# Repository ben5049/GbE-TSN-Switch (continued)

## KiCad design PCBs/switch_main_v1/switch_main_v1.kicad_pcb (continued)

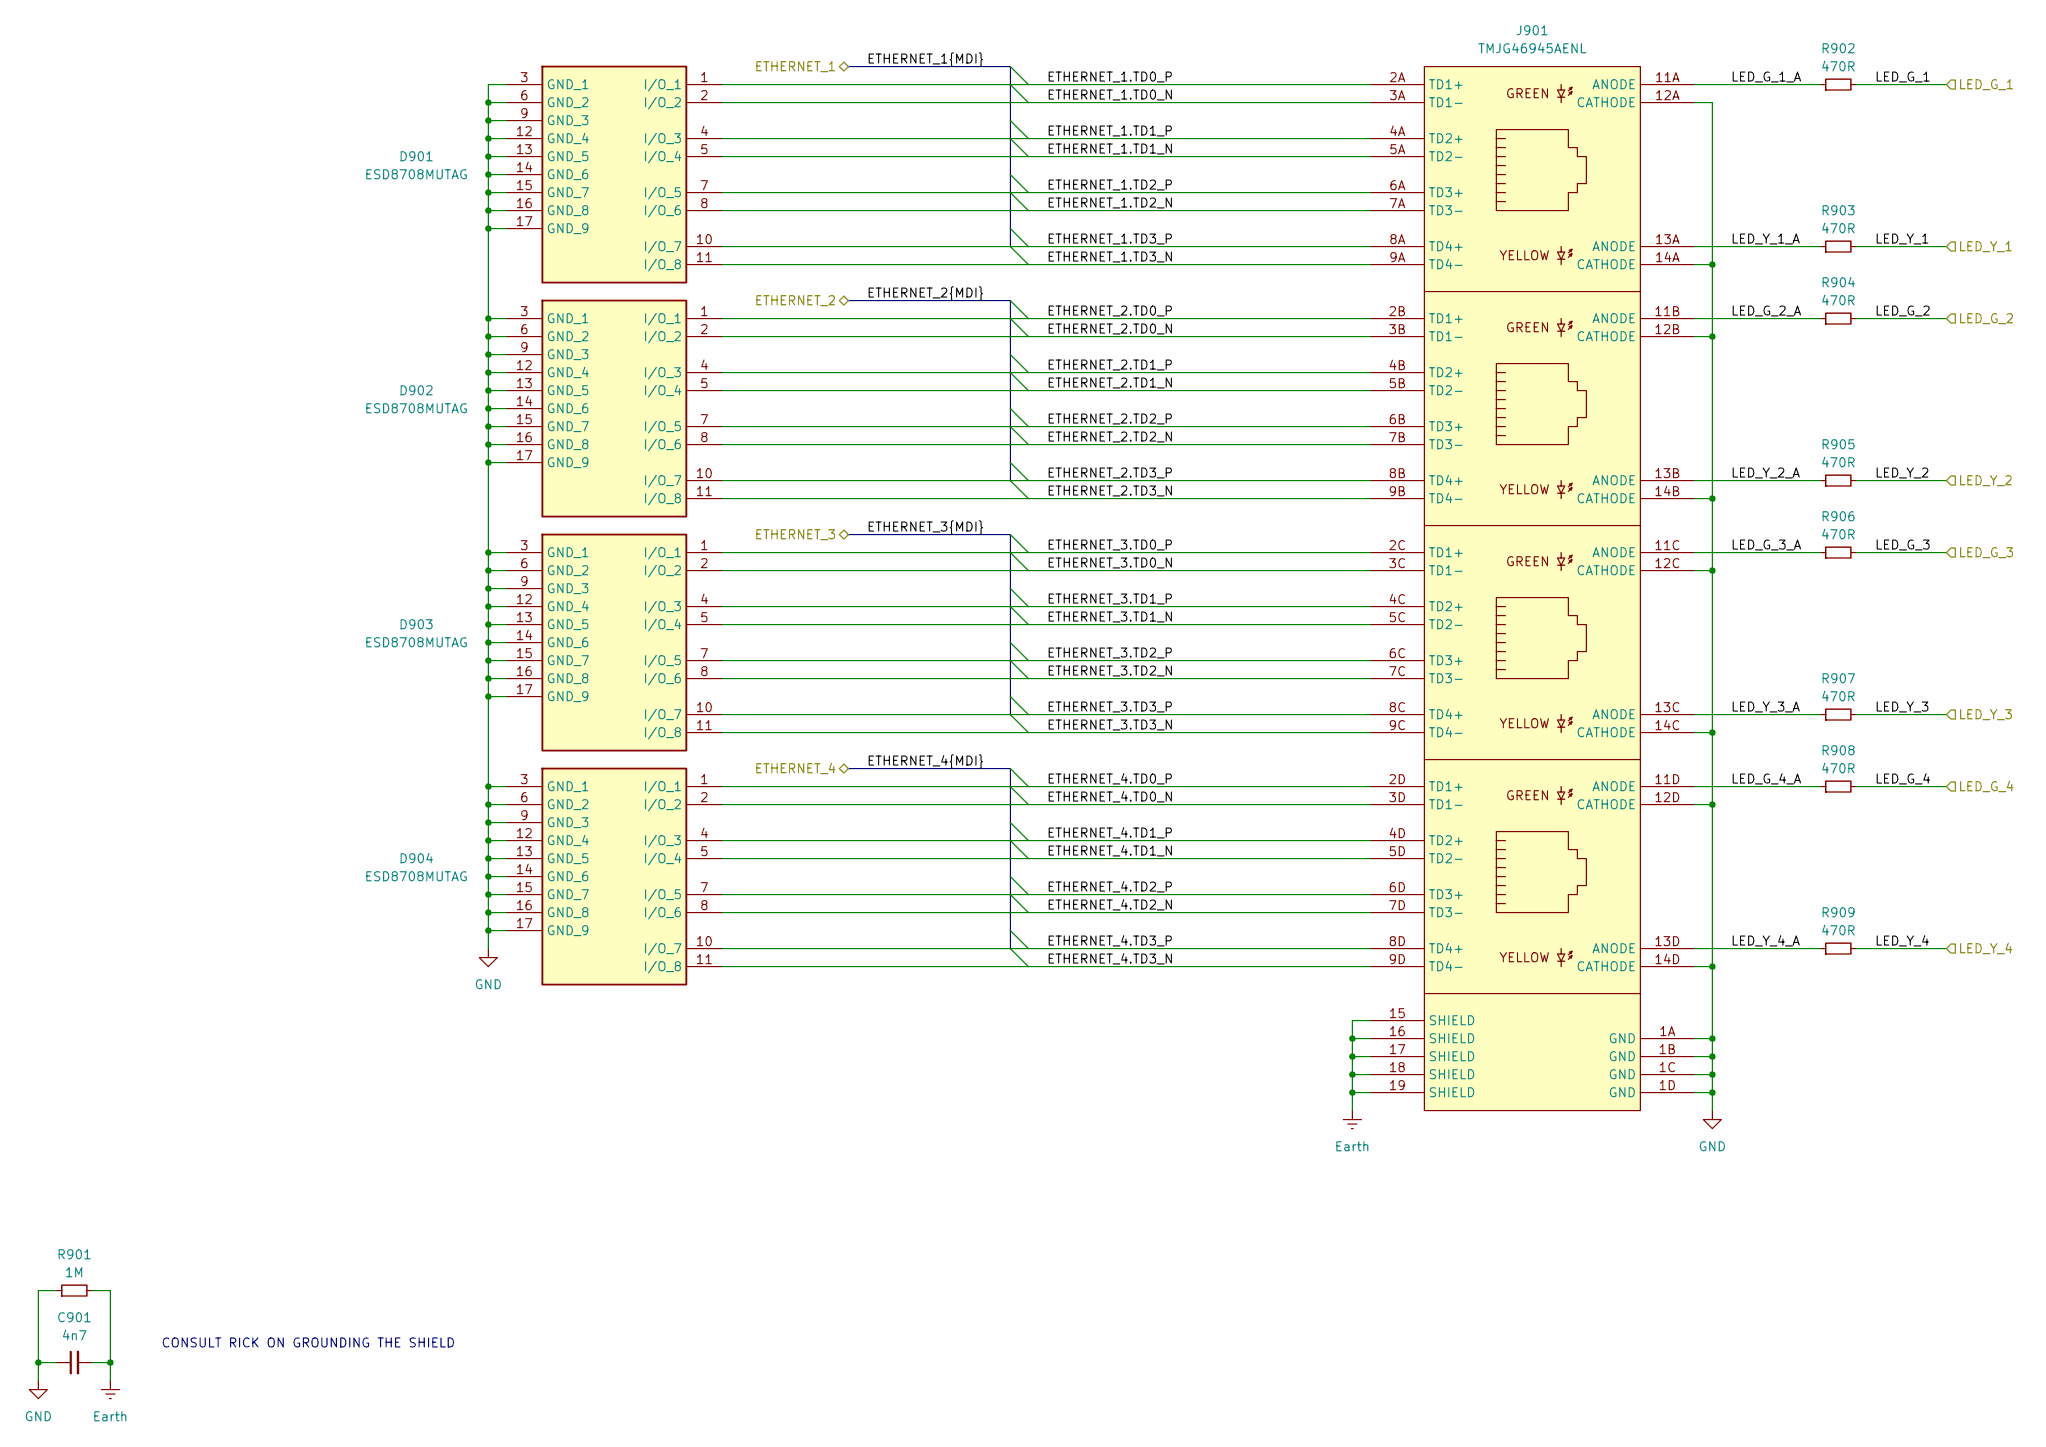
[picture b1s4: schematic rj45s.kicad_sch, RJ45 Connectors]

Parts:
C901: 4n7; C_0402_1005Metric
D901, D902, D903, D904: ESD8708MUTAG; Mouser Part Number 863-ESD8708MUTAG
J901: TMJG46945AENL
R901: 1M; R_0402_1005Metric
R902, R903, R904, R905, R906, R907, R908, R909: 470R; R_0402_1005Metric

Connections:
/ETHERNET_1.TD0_N: D901.2 (I/O_2), J901.3A (TD1-); also elsewhere on the board
/ETHERNET_1.TD0_P: D901.1 (I/O_1), J901.2A (TD1+); also elsewhere on the board
/ETHERNET_1.TD1_N: D901.5 (I/O_4), J901.5A (TD2-); also elsewhere on the board
/ETHERNET_1.TD1_P: D901.4 (I/O_3), J901.4A (TD2+); also elsewhere on the board
/ETHERNET_1.TD2_N: D901.8 (I/O_6), J901.7A (TD3-); also elsewhere on the board
/ETHERNET_1.TD2_P: D901.7 (I/O_5), J901.6A (TD3+); also elsewhere on the board
/ETHERNET_1.TD3_N: D901.11 (I/O_8), J901.9A (TD4-); also elsewhere on the board
/ETHERNET_1.TD3_P: D901.10 (I/O_7), J901.8A (TD4+); also elsewhere on the board
/ETHERNET_2.TD0_N: D902.2 (I/O_2), J901.3B (TD1-); also elsewhere on the board
/ETHERNET_2.TD0_P: D902.1 (I/O_1), J901.2B (TD1+); also elsewhere on the board
/ETHERNET_2.TD1_N: D902.5 (I/O_4), J901.5B (TD2-); also elsewhere on the board
/ETHERNET_2.TD1_P: D902.4 (I/O_3), J901.4B (TD2+); also elsewhere on the board
/ETHERNET_2.TD2_N: D902.8 (I/O_6), J901.7B (TD3-); also elsewhere on the board
/ETHERNET_2.TD2_P: D902.7 (I/O_5), J901.6B (TD3+); also elsewhere on the board
/ETHERNET_2.TD3_N: D902.11 (I/O_8), J901.9B (TD4-); also elsewhere on the board
/ETHERNET_2.TD3_P: D902.10 (I/O_7), J901.8B (TD4+); also elsewhere on the board
/ETHERNET_3.TD0_N: D903.2 (I/O_2), J901.3C (TD1-); also elsewhere on the board
/ETHERNET_3.TD0_P: D903.1 (I/O_1), J901.2C (TD1+); also elsewhere on the board
/ETHERNET_3.TD1_N: D903.5 (I/O_4), J901.5C (TD2-); also elsewhere on the board
/ETHERNET_3.TD1_P: D903.4 (I/O_3), J901.4C (TD2+); also elsewhere on the board
/ETHERNET_3.TD2_N: D903.8 (I/O_6), J901.7C (TD3-); also elsewhere on the board
/ETHERNET_3.TD2_P: D903.7 (I/O_5), J901.6C (TD3+); also elsewhere on the board
/ETHERNET_3.TD3_N: D903.11 (I/O_8), J901.9C (TD4-); also elsewhere on the board
/ETHERNET_3.TD3_P: D903.10 (I/O_7), J901.8C (TD4+); also elsewhere on the board
/ETHERNET_4.TD0_N: D904.2 (I/O_2), J901.3D (TD1-); also elsewhere on the board
/ETHERNET_4.TD0_P: D904.1 (I/O_1), J901.2D (TD1+); also elsewhere on the board
/ETHERNET_4.TD1_N: D904.5 (I/O_4), J901.5D (TD2-); also elsewhere on the board
/ETHERNET_4.TD1_P: D904.4 (I/O_3), J901.4D (TD2+); also elsewhere on the board
/ETHERNET_4.TD2_N: D904.8 (I/O_6), J901.7D (TD3-); also elsewhere on the board
/ETHERNET_4.TD2_P: D904.7 (I/O_5), J901.6D (TD3+); also elsewhere on the board
/ETHERNET_4.TD3_N: D904.11 (I/O_8), J901.9D (TD4-); also elsewhere on the board
/ETHERNET_4.TD3_P: D904.10 (I/O_7), J901.8D (TD4+); also elsewhere on the board
/LED_G_1: R902.2; also elsewhere on the board
/LED_G_2: R904.2; also elsewhere on the board
/LED_G_3: R906.2; also elsewhere on the board
/LED_G_4: R908.2; also elsewhere on the board
/LED_Y_1: R903.2; also elsewhere on the board
/LED_Y_2: R905.2; also elsewhere on the board
/LED_Y_3: R907.2; also elsewhere on the board
/LED_Y_4: R909.2; also elsewhere on the board
/RJ45s/LED_G_1_A: J901.11A (ANODE), R902.1
/RJ45s/LED_G_2_A: J901.11B (ANODE), R904.1
/RJ45s/LED_G_3_A: J901.11C (ANODE), R906.1
/RJ45s/LED_G_4_A: J901.11D (ANODE), R908.1
/RJ45s/LED_Y_1_A: J901.13A (ANODE), R903.1
/RJ45s/LED_Y_2_A: J901.13B (ANODE), R905.1
/RJ45s/LED_Y_3_A: J901.13C (ANODE), R907.1
/RJ45s/LED_Y_4_A: J901.13D (ANODE), R909.1
Earth: C901.2, J901.15 (SHIELD), J901.16 (SHIELD), J901.17 (SHIELD), J901.18 (SHIELD), J901.19 (SHIELD), R901.2; also elsewhere on the board
GND: C901.1, D901.3 (GND_1), D901.6 (GND_2), D901.9 (GND_3), D901.12 (GND_4), D901.13 (GND_5), D901.14 (GND_6), D901.15 (GND_7), D901.16 (GND_8), D901.17 (GND_9), D902.3 (GND_1), D902.6 (GND_2), D902.9 (GND_3), D902.12 (GND_4), D902.13 (GND_5), D902.14 (GND_6), D902.15 (GND_7), D902.16 (GND_8), D902.17 (GND_9), D903.3 (GND_1), D903.6 (GND_2), D903.9 (GND_3), D903.12 (GND_4), D903.13 (GND_5), D903.14 (GND_6), D903.15 (GND_7), D903.16 (GND_8), D903.17 (GND_9), D904.3 (GND_1), D904.6 (GND_2), D904.9 (GND_3), D904.12 (GND_4), D904.13 (GND_5), D904.14 (GND_6), D904.15 (GND_7), D904.16 (GND_8), D904.17 (GND_9), J901.1A (GND), J901.1B (GND), J901.1C (GND), J901.1D (GND), J901.12A (CATHODE), J901.12B (CATHODE), J901.12C (CATHODE), J901.12D (CATHODE), J901.14A (CATHODE), J901.14B (CATHODE), J901.14C (CATHODE), J901.14D (CATHODE), R901.1; also elsewhere on the board

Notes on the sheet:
CONSULT RICK ON GROUNDING THE SHIELD

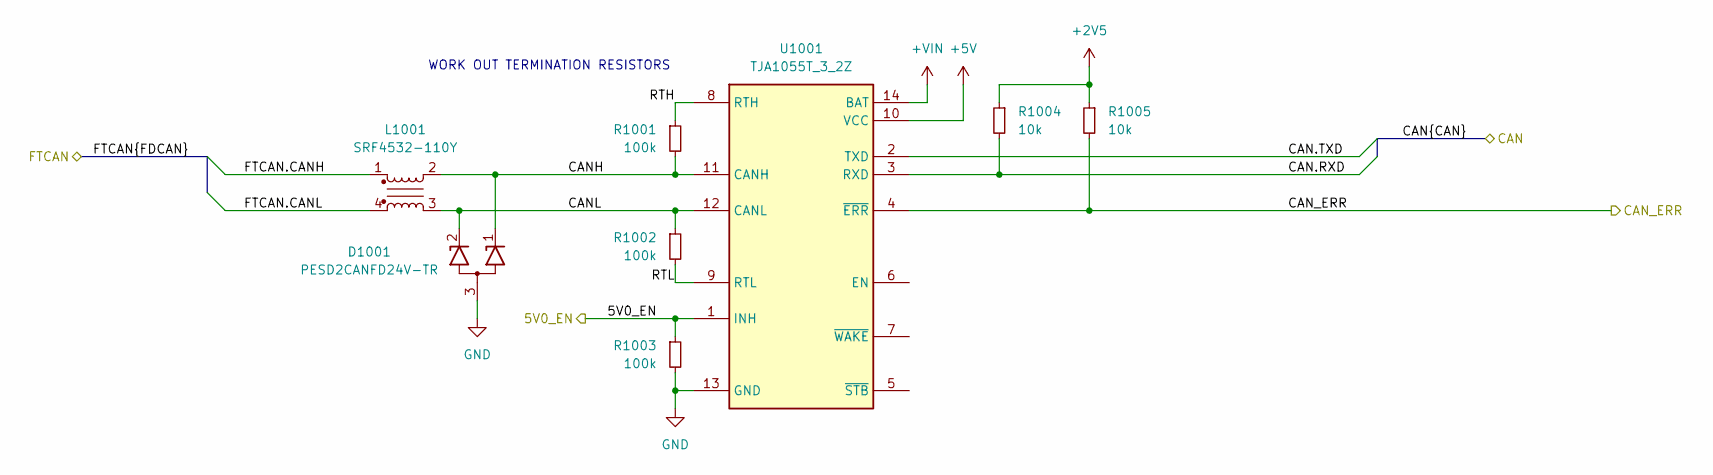
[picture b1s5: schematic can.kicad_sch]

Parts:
D1001: PESD2CANFD24V-TR; SOT95P230X110-3N; Mouser Part Number 771-PESD2CANFD24V-TR
L1001: SRF4532-110Y; SRF4532101Y; Mouser Part Number 652-SRF4532-110Y
R1001, R1002, R1003: 100k; R_0402_1005Metric
R1004, R1005: 10k; R_0402_1005Metric
U1001: TJA1055T_3_2Z; SOIC127P600X175-14N; Mouser Part Number 771-TJA1055T/3/2Z

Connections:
+2V5: R1004.1, R1005.1; also elsewhere on the board
+5V: U1001.10 (VCC)
+VIN: U1001.14 (BAT); also elsewhere on the board
/5V0_EN: R1003.1, U1001.1 (INH); also elsewhere on the board
/CAN.RXD: R1004.2, U1001.3 (RXD); also elsewhere on the board
/CAN.TXD: U1001.2 (TXD); also elsewhere on the board
/CAN/CANH: D1001.1 (K1), L1001.2, R1001.2, U1001.11 (CANH)
/CAN/CANL: D1001.2 (K2), L1001.3, R1002.1, U1001.12 (CANL)
/CAN/CAN_ERR: R1005.2, U1001.4 (~ERR)
/CAN/FTCAN.CANH: L1001.1
/CAN/FTCAN.CANL: L1001.4
/CAN/RTH: R1001.1, U1001.8 (RTH)
/CAN/RTL: R1002.2, U1001.9 (RTL)
GND: D1001.3 (CC), R1003.2, U1001.13 (GND); also elsewhere on the board

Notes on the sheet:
WORK OUT TERMINATION RESISTORS

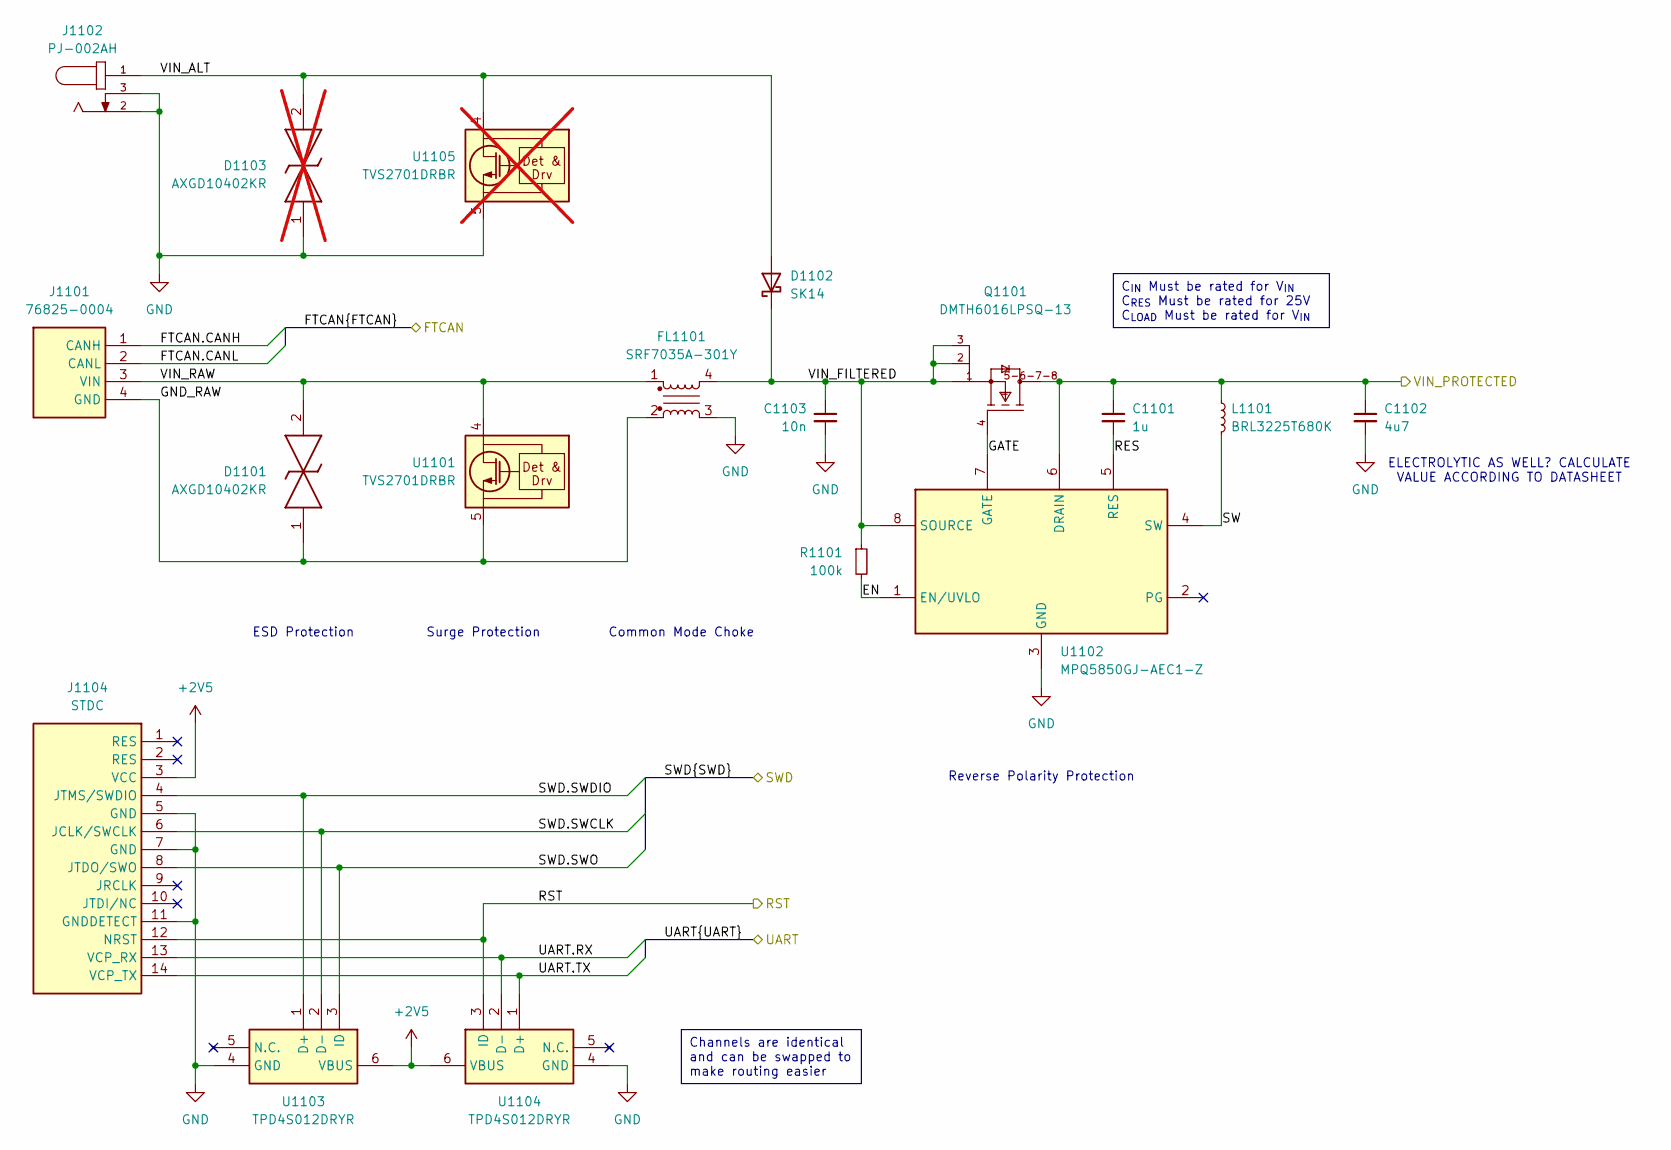
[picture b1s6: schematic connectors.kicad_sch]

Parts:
C1101: 1u; C_0402_1005Metric
C1102: 4u7; C_0402_1005Metric
C1103: 10n; C_0402_1005Metric
D1101: AXGD10402KR; DIONM105X51N; Mouser Part Number 576-AXGD10402KR
D1102: SK14; D_SMA
D1103: AXGD10402KR; DIONM105X51N; Mouser Part Number 576-AXGD10402KR; not fitted
FL1101: SRF7035A-301Y; SRF7035A301Y; Mouser Part Number 652-SRF7035A-301Y
J1101: 76825-0004; 768250004; Mouser Part Number 538-76825-0004
J1102: PJ-002AH; CUI_PJ-002AH
J1104: STDC; STDC14
L1101: BRL3225T680K; L_1210_3225Metric
Q1101: DMTH6016LPSQ-13; Diodes_Incorporated-PowerDI5060-8-03_2017-0-MFG; mouser part number 621-DMTH6016LPSQ-13; digikey description MOSFET N-CHA 60V 10.6A POWERDI
R1101: 100k; R_0402_1005Metric
U1101: TVS2701DRBR; SON65P300X300X100-9N-D; Mouser Part Number 595-TVS2701DRBR
U1102: MPQ5850GJ-AEC1-Z; SOT65P280X100-8N; Manufacturer_Part_Number MPQ5850GJ-AEC1-Z
U1103, U1104: TPD4S012DRYR; Mouser Part Number 595-TPD4S012DRYR
U1105: TVS2701DRBR; SON65P300X300X100-9N-D; Mouser Part Number 595-TVS2701DRBR; not fitted

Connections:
+2V5: J1104.3 (VCC), U1103.6 (VBUS), U1104.6 (VBUS); also elsewhere on the board
/Connectors/EN: R1101.2, U1102.1 (EN/UVLO)
/Connectors/GATE: Q1101.4 (G), U1102.7 (GATE)
/Connectors/GND_RAW: D1101.1, FL1101.2, J1101.4 (GND), U1101.5 (GND), U1101.6 (GND), U1101.7 (GND), U1101.8 (GND)
/Connectors/RES: C1101.2, U1102.5 (RES)
/Connectors/SW: L1101.2, U1102.4 (SW)
/Connectors/VIN_ALT: D1102.2 (A), D1103.2, J1102.1, U1105.1 (IN), U1105.2 (IN), U1105.3 (IN), U1105.4 (IN)
/Connectors/VIN_FILTERED: C1103.1, D1102.1 (K), FL1101.4, Q1101.1 (S), Q1101.2 (S), Q1101.3 (S), R1101.1, U1102.8 (SOURCE)
/Connectors/VIN_PROTECTED: C1101.1, C1102.1, L1101.1, Q1101.5-6-7-8 (D), U1102.6 (DRAIN); also elsewhere on the board
/Connectors/VIN_RAW: D1101.2, FL1101.1, J1101.3 (VIN), U1101.1 (IN), U1101.2 (IN), U1101.3 (IN), U1101.4 (IN)
/FTCAN.CANH: J1101.1 (CANH)
/FTCAN.CANL: J1101.2 (CANL)
/MCU_RST: J1104.12 (NRST), U1104.3 (ID); also elsewhere on the board
/SWD.SWCLK: J1104.6 (JCLK/SWCLK), U1103.2 (D-); also elsewhere on the board
/SWD.SWDIO: J1104.4 (JTMS/SWDIO), U1103.1 (D+); also elsewhere on the board
/SWD.SWO: J1104.8 (JTDO/SWO), U1103.3 (ID); also elsewhere on the board
/UART.RX: J1104.13 (VCP_RX), U1104.2 (D-)
/UART.TX: J1104.14 (VCP_TX), U1104.1 (D+)
GND: C1102.2, C1103.2, D1103.1, FL1101.3, J1102.2, J1102.3, J1104.5 (GND), J1104.7 (GND), J1104.11 (GNDDETECT), U1102.3 (GND), U1103.4 (GND), U1104.4 (GND), U1105.5 (GND), U1105.6 (GND), U1105.7 (GND), U1105.8 (GND); also elsewhere on the board

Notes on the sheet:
Channels are identical and can be swapped to make routing easier
C_{IN} Must be rated for V_{IN} C_{RES} Must be rated for 25V C_{LOAD} Must be rated for V_{IN}
Surge Protection
Common Mode Choke
ESD Protection
ELECTROLYTIC AS WELL? CALCULATE VALUE ACCORDING TO DATASHEET
Reverse Polarity Protection

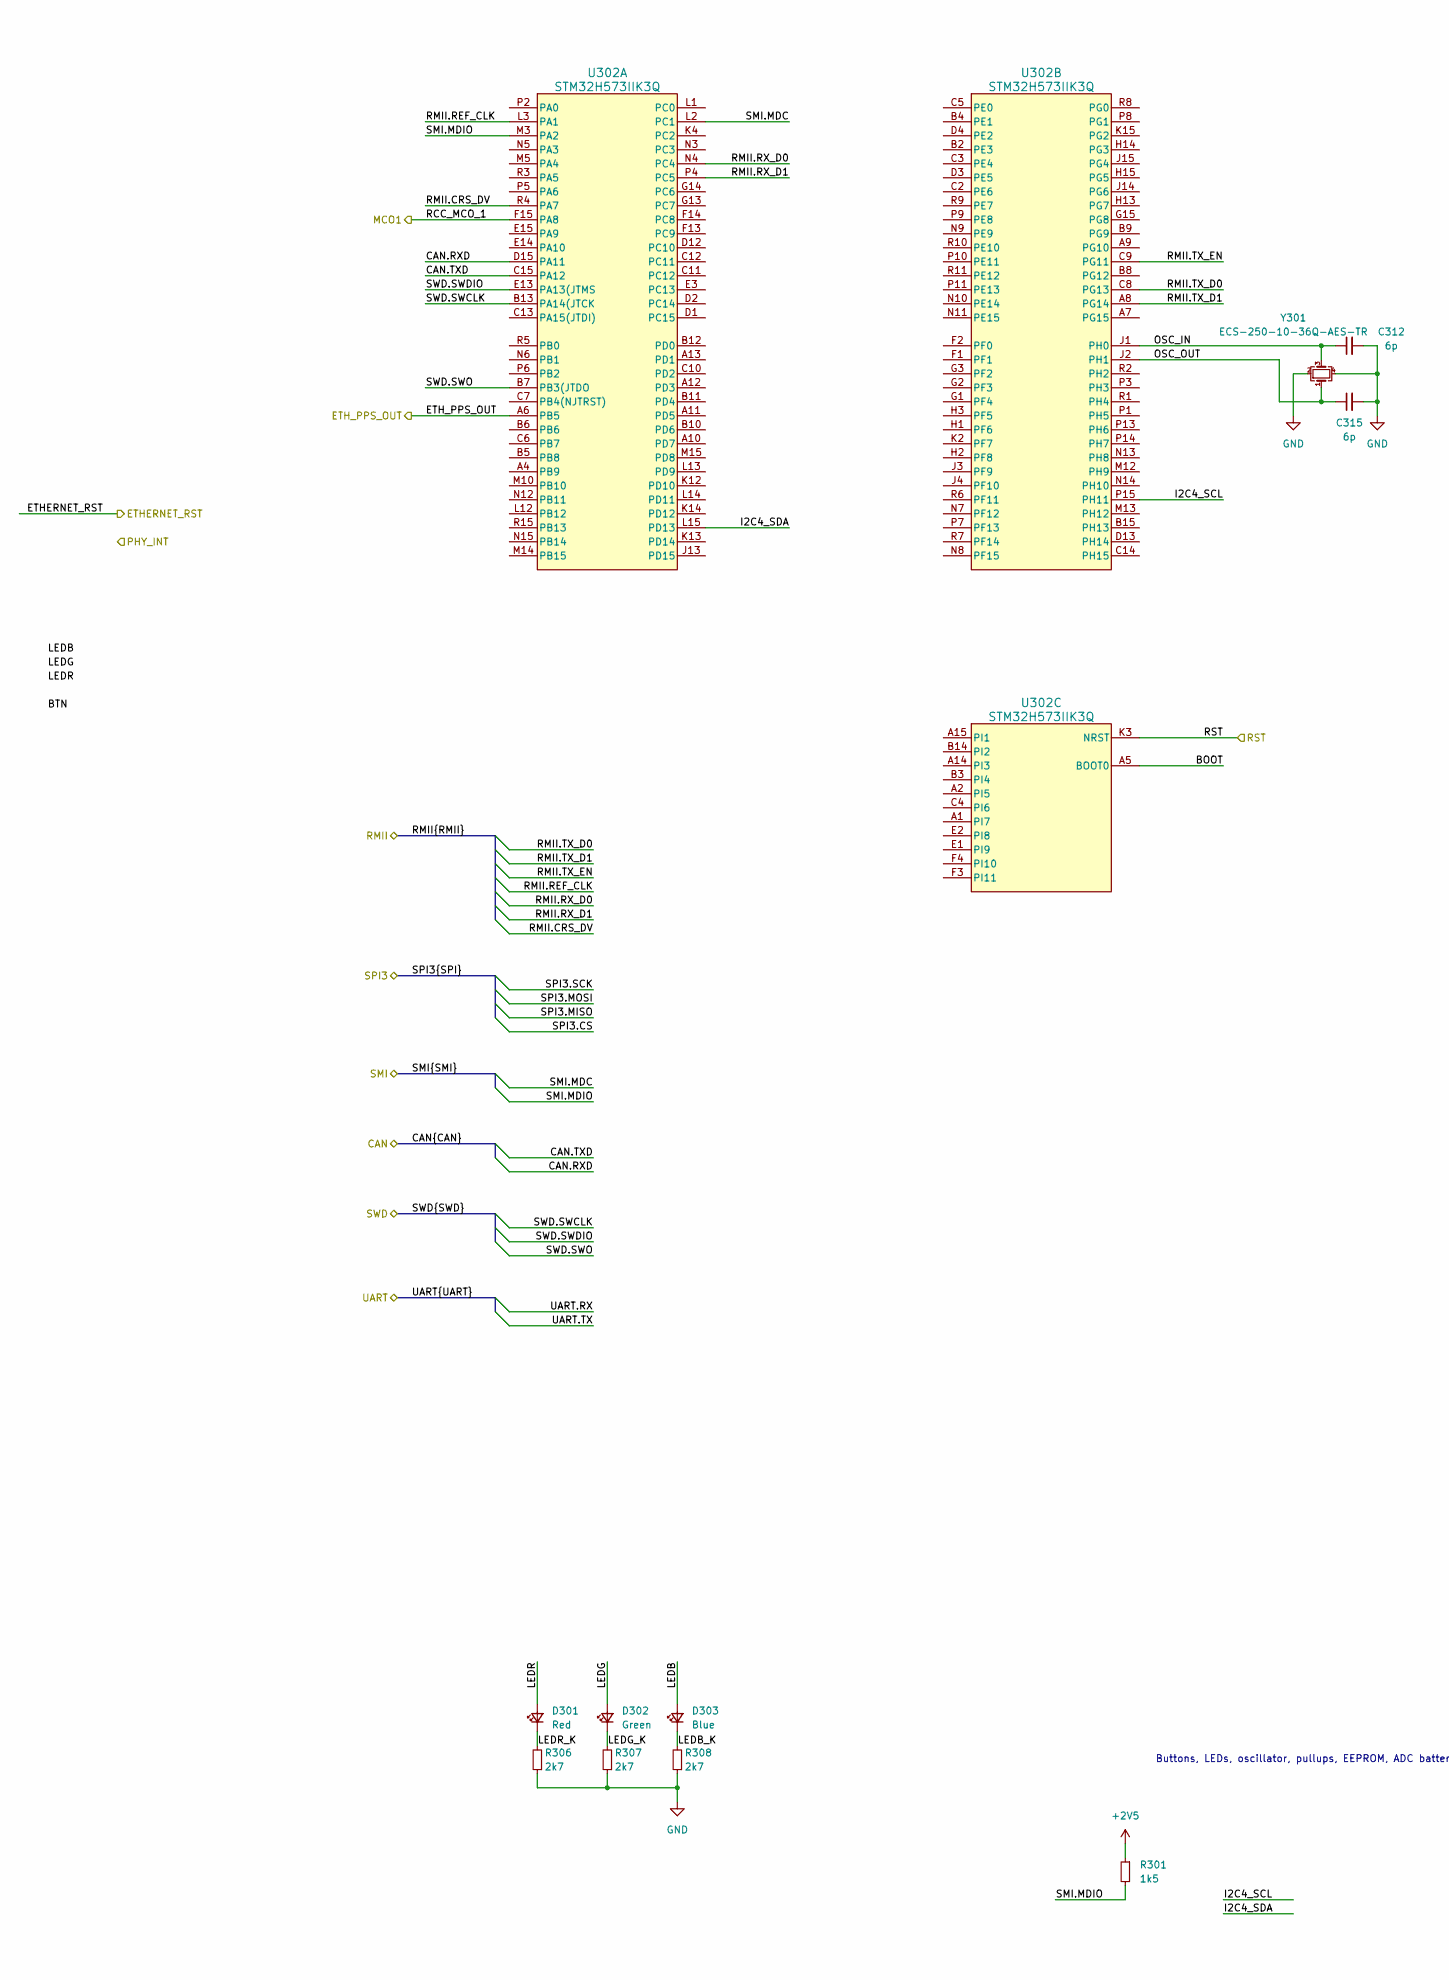
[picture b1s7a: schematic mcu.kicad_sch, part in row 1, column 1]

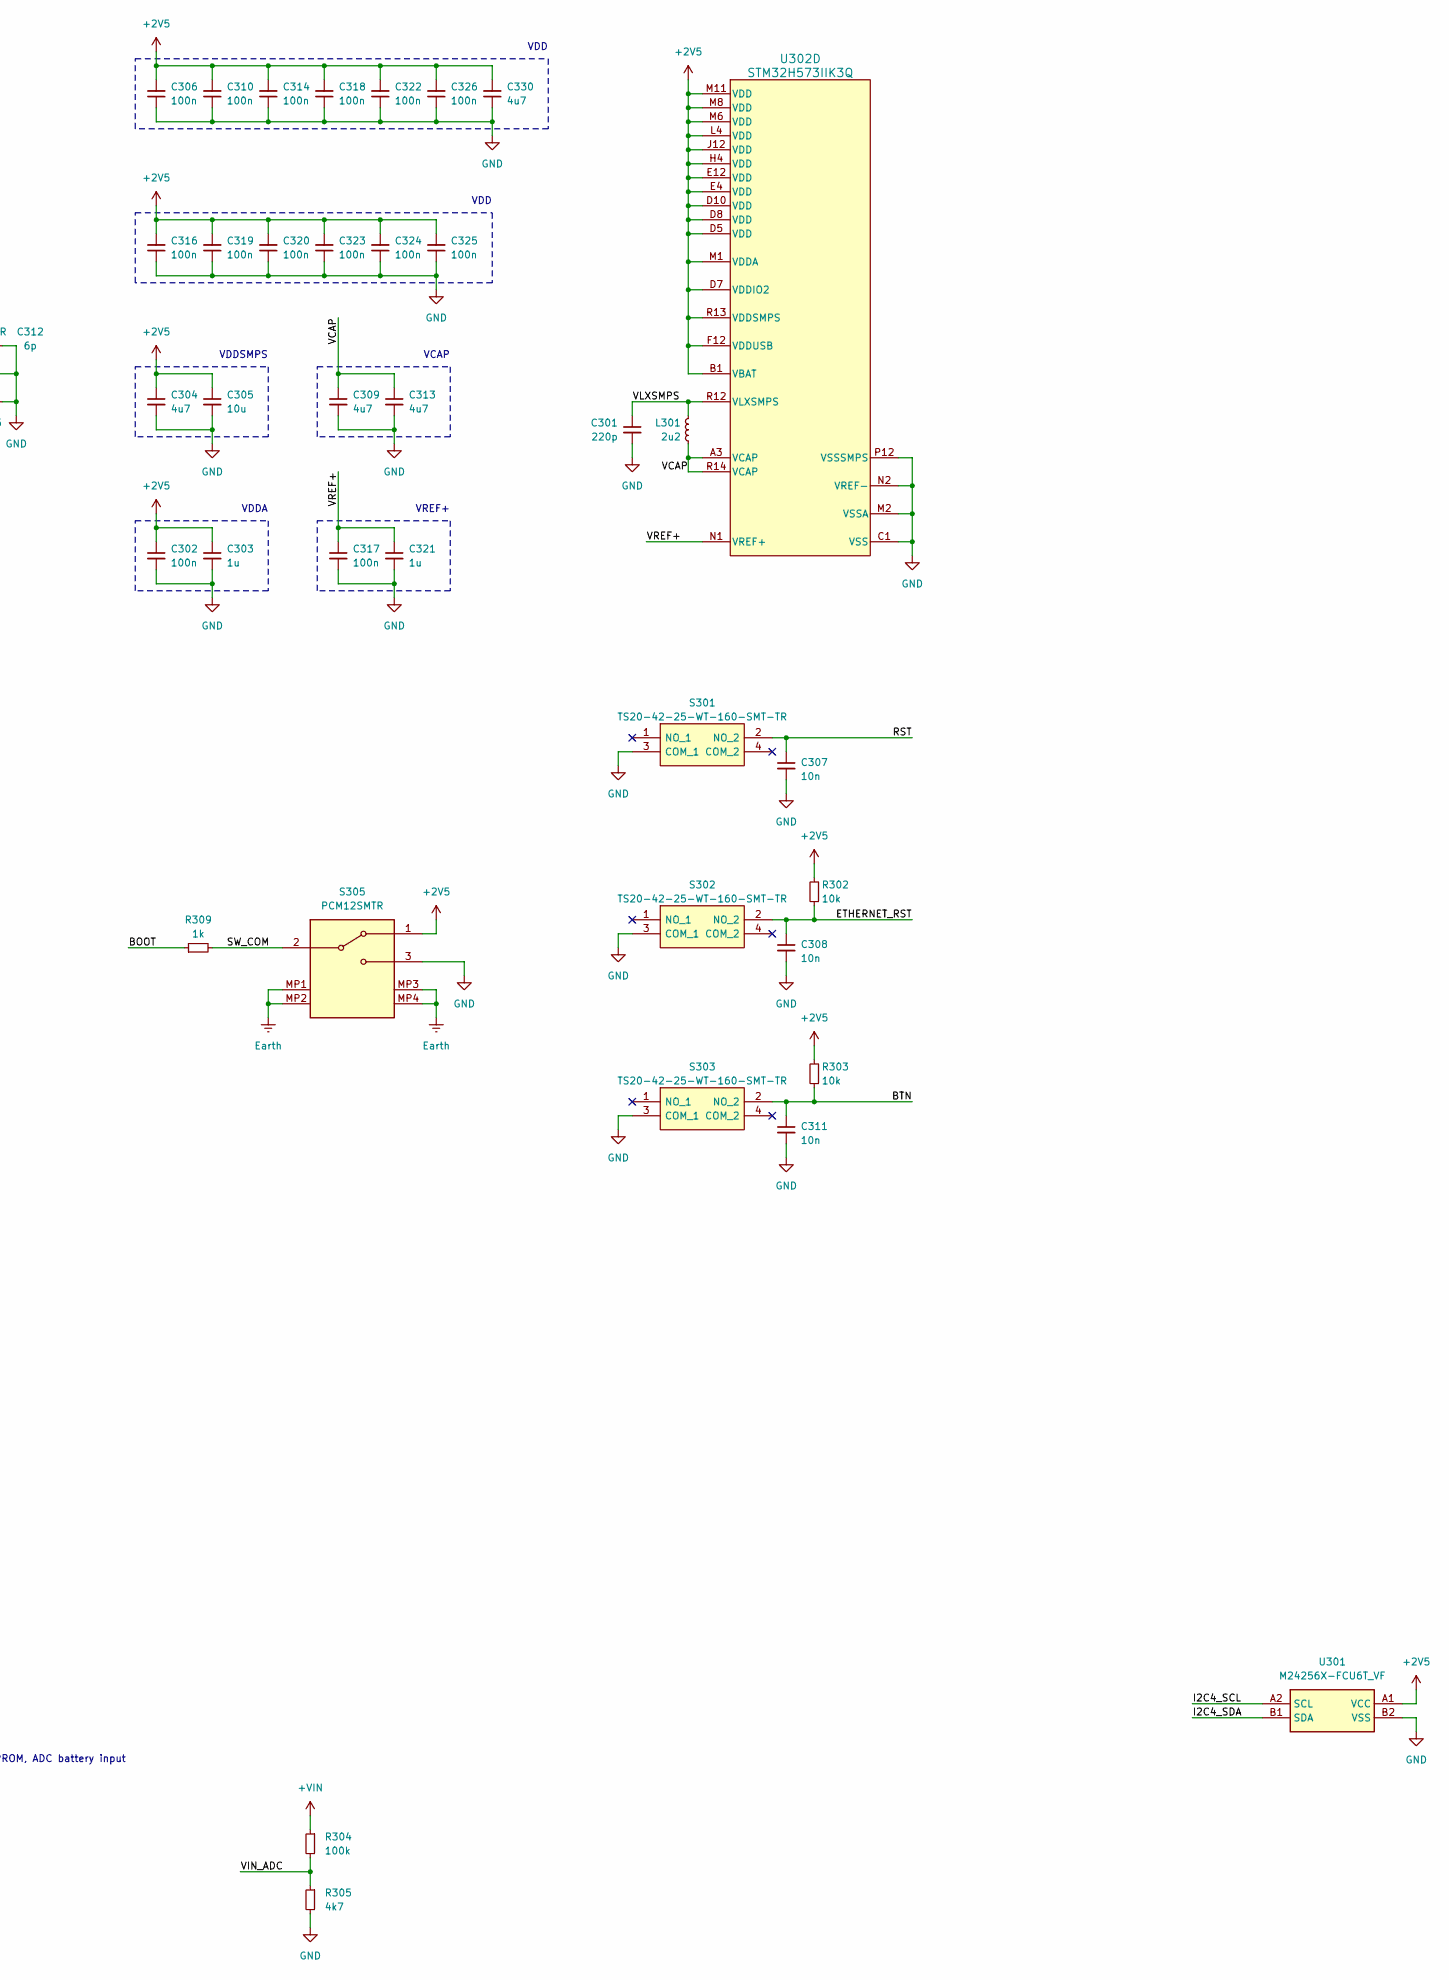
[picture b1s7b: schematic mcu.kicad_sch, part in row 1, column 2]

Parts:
C301: 220p; C_0402_1005Metric
C302, C306, C310, C314, C316, C317, C318, C319, C320, C322, C323, C324, C325, C326: 100n; C_0402_1005Metric
C303, C321: 1u; C_0402_1005Metric
C304, C309, C313, C330: 4u7; C_0402_1005Metric
C305: 10u; C_0402_1005Metric
C307, C308, C311: 10n; C_0402_1005Metric
C312, C315: 6p; C_0402_1005Metric
D301: Red; LED_0402_1005Metric
D302: Green; LED_0402_1005Metric
D303: Blue; LED_0402_1005Metric
L301: 2u2; L_Murata_DFE201610P
R301: 1k5; R_0402_1005Metric
R302, R303: 10k; R_0402_1005Metric
R304: 100k; R_0402_1005Metric
R305: 4k7; R_0402_1005Metric
R306, R307, R308: 2k7; R_0402_1005Metric
R309: 1k; R_0402_1005Metric
S301, S302, S303: TS20-42-25-WT-160-SMT-TR; TS204225WT160SMTTRMSL; Mouser Part Number 179-TS204225WT160SMT
S305: PCM12SMTR; Mouser Part Number 611-PCM12SMTR
U301: M24256X-FCU6T_VF; BGA4C50P2X2_70X98X33; Mouser Part Number 511-M24256X-FCU6T/VF
U302: STM32H573IIK3Q
Y301: ECS-250-10-36Q-AES-TR; Crystal_SMD_2520-4Pin_2.5x2.0mm

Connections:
+2V5: C302.1, C303.1, C304.1, C305.1, C306.2, C310.2, C314.2, C316.2, C318.2, C319.2, C320.2, C322.2, C323.2, C324.2, C325.2, C326.2, C330.2, R301.1, R302.2, R303.2, S305.1 (A), U301.A1 (VCC), U302.B1 (VBAT), U302.D5 (VDD), U302.D7 (VDDIO2), U302.D8 (VDD), U302.D10 (VDD), U302.E4 (VDD), U302.E12 (VDD), U302.F12 (VDDUSB), U302.H4 (VDD), U302.J12 (VDD), U302.L4 (VDD), U302.M1 (VDDA), U302.M6 (VDD), U302.M8 (VDD), U302.M11 (VDD), U302.R13 (VDDSMPS); also elsewhere on the board
+VIN: R304.1; also elsewhere on the board
/CAN.RXD: U302.D15 (PA11); also elsewhere on the board
/CAN.TXD: U302.C15 (PA12); also elsewhere on the board
/ETHERNET_RST: C308.1, R302.1, S302.2 (NO_2); also elsewhere on the board
/MCU/BOOT: R309.1, U302.A5 (BOOT0)
/MCU/BTN: C311.1, R303.1, S303.2 (NO_2)
/MCU/I2C4_SCL: U301.A2 (SCL), U302.P15 (PH11)
/MCU/I2C4_SDA: U301.B1 (SDA), U302.L15 (PD13)
/MCU/LEDB: D303.2 (A)
/MCU/LEDB_K: D303.1 (K), R308.2
/MCU/LEDG: D302.2 (A)
/MCU/LEDG_K: D302.1 (K), R307.2
/MCU/LEDR: D301.2 (A)
/MCU/LEDR_K: D301.1 (K), R306.2
/MCU/OSC_IN: C312.1, U302.J1 (PH0), Y301.3
/MCU/OSC_OUT: C315.1, U302.J2 (PH1), Y301.1
/MCU/SW_COM: R309.2, S305.2 (B)
/MCU/VCAP: C309.1, C313.1, L301.2, U302.A3 (VCAP), U302.R14 (VCAP)
/MCU/VIN_ADC: R304.2, R305.1
/MCU/VLXSMPS: C301.1, L301.1, U302.R12 (VLXSMPS)
/MCU/VREF+: C317.1, C321.1, U302.N1 (VREF+)
/MCU_RST: C307.1, S301.2 (NO_2), U302.K3 (NRST); also elsewhere on the board
/PTP_CLK: U302.A6 (PB5); also elsewhere on the board
/RMII.CRS_DV: U302.R4 (PA7); also elsewhere on the board
/RMII.REF_CLK: U302.L3 (PA1); also elsewhere on the board
/RMII.RX_D0: U302.N4 (PC4); also elsewhere on the board
/RMII.RX_D1: U302.P4 (PC5); also elsewhere on the board
/RMII.TX_D0: U302.C8 (PG13); also elsewhere on the board
/RMII.TX_D1: U302.A8 (PG14); also elsewhere on the board
/RMII.TX_EN: U302.C9 (PG11); also elsewhere on the board
/SMI.MDC: U302.L2 (PC1); also elsewhere on the board
/SMI.MDIO: R301.2, U302.M3 (PA2); also elsewhere on the board
/SWD.SWCLK: U302.B13 (PA14(JTCK); also elsewhere on the board
/SWD.SWDIO: U302.E13 (PA13(JTMS); also elsewhere on the board
/SWD.SWO: U302.B7 (PB3(JTDO); also elsewhere on the board
/SWITCH_CLK: U302.F15 (PA8); also elsewhere on the board
Earth: S305.MP1, S305.MP2, S305.MP3, S305.MP4; also elsewhere on the board
GND: C301.2, C302.2, C303.2, C304.2, C305.2, C306.1, C307.2, C308.2, C309.2, C310.1, C311.2, C312.2, C313.2, C314.1, C315.2, C316.1, C317.2, C318.1, C319.1, C320.1, C321.2, C322.1, C323.1, C324.1, C325.1, C326.1, C330.1, R305.2, R306.1, R307.1, R308.1, S301.3 (COM_1), S302.3 (COM_1), S303.3 (COM_1), S305.3 (C), U301.B2 (VSS), U302.C1 (VSS), U302.D6 (VSS), U302.D9 (VSS), U302.D11 (VSS), U302.D14 (VSS), U302.F6 (VSS), U302.F7 (VSS), U302.F8 (VSS), U302.F9 (VSS), U302.F10 (VSS), U302.G4 (VSS), U302.G6 (VSS), U302.G7 (VSS), U302.G8 (VSS), U302.G9 (VSS), U302.G10 (VSS), U302.G12 (VSS), U302.H6 (VSS), U302.H7 (VSS), U302.H8 (VSS), U302.H9 (VSS), U302.H10 (VSS), U302.H12 (VSS), U302.J6 (VSS), U302.J7 (VSS), U302.J8 (VSS), U302.J9 (VSS), U302.J10 (VSS), U302.K1 (VSS), U302.K6 (VSS), U302.K7 (VSS), U302.K8 (VSS), U302.K9 (VSS), U302.K10 (VSS), U302.M2 (VSSA), U302.M4 (VSS), U302.M7 (VSS), U302.M9 (VSS), U302.N2 (VREF-), U302.P12 (VSSSMPS), Y301.2, Y301.4; also elsewhere on the board

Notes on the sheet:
VDD
VDDA
Buttons, LEDs, oscillator, pullups, EEPROM, ADC battery input
VDDSMPS
VREF+
VCAP

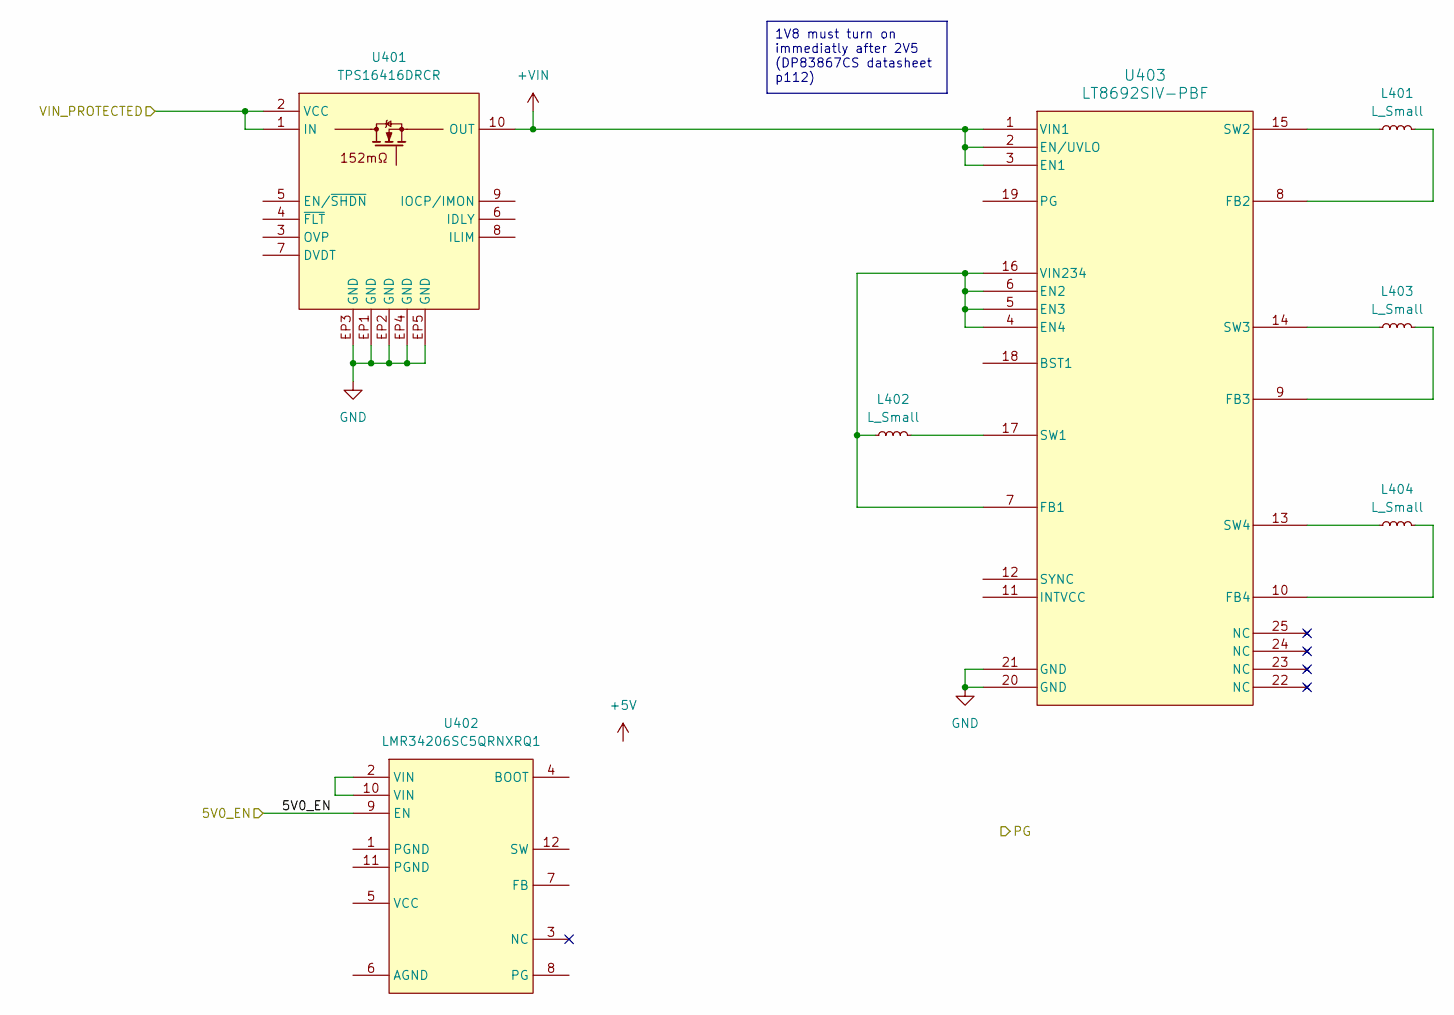
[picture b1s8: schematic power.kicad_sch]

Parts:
L401, L402, L403, L404: L_Small
U401: TPS16416DRCR; TPS74901DRCR; Mouser Part Number 595-TPS16416DRCR
U402: LMR34206SC5QRNXRQ1; CONV_LMR33620BRNXT
U403: LT8692SIV-PBF; LT8692SIV_PBF

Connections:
+VIN: U401.10 (OUT), U403.1 (VIN1), U403.2 (EN/UVLO), U403.3 (EN1); also elsewhere on the board
/5V0_EN: U402.9 (EN); also elsewhere on the board
/Connectors/VIN_PROTECTED: U401.1 (IN), U401.2 (VCC); also elsewhere on the board
GND: U401.EP1 (GND), U401.EP2 (GND), U401.EP3 (GND), U401.EP4 (GND), U401.EP5 (GND), U403.20 (GND), U403.21 (GND); also elsewhere on the board
unnamed: U402.2 (VIN), U402.10 (VIN)
unnamed: L402.1, U403.4 (EN4), U403.5 (EN3), U403.6 (EN2), U403.7 (FB1), U403.16 (VIN234)
unnamed: L401.2, U403.8 (FB2)
unnamed: L403.2, U403.9 (FB3)
unnamed: L404.2, U403.10 (FB4)
unnamed: L402.2, U403.17 (SW1)
unnamed: L401.1, U403.15 (SW2)
unnamed: L403.1, U403.14 (SW3)
unnamed: L404.1, U403.13 (SW4)

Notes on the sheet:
1V8 must turn on immediatly after 2V5 (DP83867CS datasheet p112)

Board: 2 copper layers, 290 parts (0 on the bottom side), 173 nets, no tracks yet.

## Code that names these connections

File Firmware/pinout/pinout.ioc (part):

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Mcu.Name=STM32H573IIKxQ
Mcu.Package=UFBGA176
Mcu.UserName=STM32H573IIKxQ
PA1.Mode=RMII_PTP_Synchro
PA1.Signal=ETH_REF_CLK
PA11.Mode=FDCAN_Activate
PA11.Signal=FDCAN1_RX
PA12.Mode=FDCAN_Activate
PA12.Signal=FDCAN1_TX
PA13(JTMS/SWDIO).Mode=Trace_Asynchronous_SW
PA13(JTMS/SWDIO).Signal=DEBUG_JTMS-SWDIO
PA14(JTCK/SWCLK).Mode=Trace_Asynchronous_SW
PA14(JTCK/SWCLK).Signal=DEBUG_JTCK-SWCLK
PA2.Mode=RMII_PTP_Synchro
PA2.Signal=ETH_MDIO
PA7.Mode=RMII_PTP_Synchro
PA7.Signal=ETH_CRS_DV
PA8.Mode=Clock-out
PA8.Signal=RCC_MCO_1
PB3(JTDO/TRACESWO).Mode=Trace_Asynchronous_SW
PB3(JTDO/TRACESWO).Signal=DEBUG_JTDO-SWO
PB5.Mode=RMII_PTP_Synchro
PB5.Signal=ETH_PPS_OUT
PC1.Mode=RMII_PTP_Synchro
PC1.Signal=ETH_MDC
PC4.Mode=RMII_PTP_Synchro
PC4.Signal=ETH_RXD0
PC5.Mode=RMII_PTP_Synchro
PC5.Signal=ETH_RXD1
PD13.Mode=I2C
PD13.Signal=I2C4_SDA
PG11.Mode=RMII_PTP_Synchro
PG11.Signal=ETH_TX_EN
PG13.Mode=RMII_PTP_Synchro
PG13.Signal=ETH_TXD0
PG14.Mode=RMII_PTP_Synchro
PG14.Signal=ETH_TXD1
PH0-OSC_IN(PH0).Mode=HSE-External-Oscillator
PH0-OSC_IN(PH0).Signal=RCC_OSC_IN
PH1-OSC_OUT(PH1).Mode=HSE-External-Oscillator
PH1-OSC_OUT(PH1).Signal=RCC_OSC_OUT
PH11.Mode=I2C
PH11.Signal=I2C4_SCL
RCC.HSE_VALUE=25000000
RCC.SYSCLKFreq_VALUE=250000000
RCC.SYSCLKSource=RCC_SYSCLKSOURCE_PLLCLK
board=custom

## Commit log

2024-04-04 Created folders and updated .gitignore
2024-04-05 System architecture chosen. Schematic started.
2024-04-05 Connectors schematic almost complete
2024-04-06 Added schematic annotations
2024-04-06 Schematic progress
2024-04-07 Block diagram layout change
2024-04-07 GbE part of schematic done
2024-04-08 Common mode choke needed on power input
2024-04-09 Progress on CAN schematic sheet
2024-04-10 Changed MCU to STM32H573VIT3Q
2024-04-11 Changed MCU to STM32H573IIK3Q
